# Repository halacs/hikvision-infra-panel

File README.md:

# Infra panel designs Hikvision IP cameras

After a few months/years infra LEDs are gone and need to be replaced. Since there are no cheap replacement boards on the internet I made my own based on the original factory infra panel.

I used KiCad 8.0 and Ubuntu 22.04 LTS. I add the final gerber finels and some pictures as well to the repository.

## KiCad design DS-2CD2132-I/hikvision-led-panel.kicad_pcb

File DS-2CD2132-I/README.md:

# Infra panel for Hikvision DS-2CD2132-I

However, I designed this infra panel for my Hikvision DS-2CD2132-I cameras, it might fit for other Hikvision models too. I have no experience with other models yet. If you have please let me know, either via a pull request or in any other way. Thanks!

I noticed that I drawn my PCB maybe with too thin wirings so be careful with the lines near to the edges of the PCB. I cut one line off while I was placing the parts...

# Parts

- 1 pc socket: JOINT TECH A1250WV-4P
- 30 pcs 3mm 850 nm infrared LEDs
- 1 pcs BPV10NF 5mm 950nm photodiode (or L-93DP3BT 3mm phototransistor)

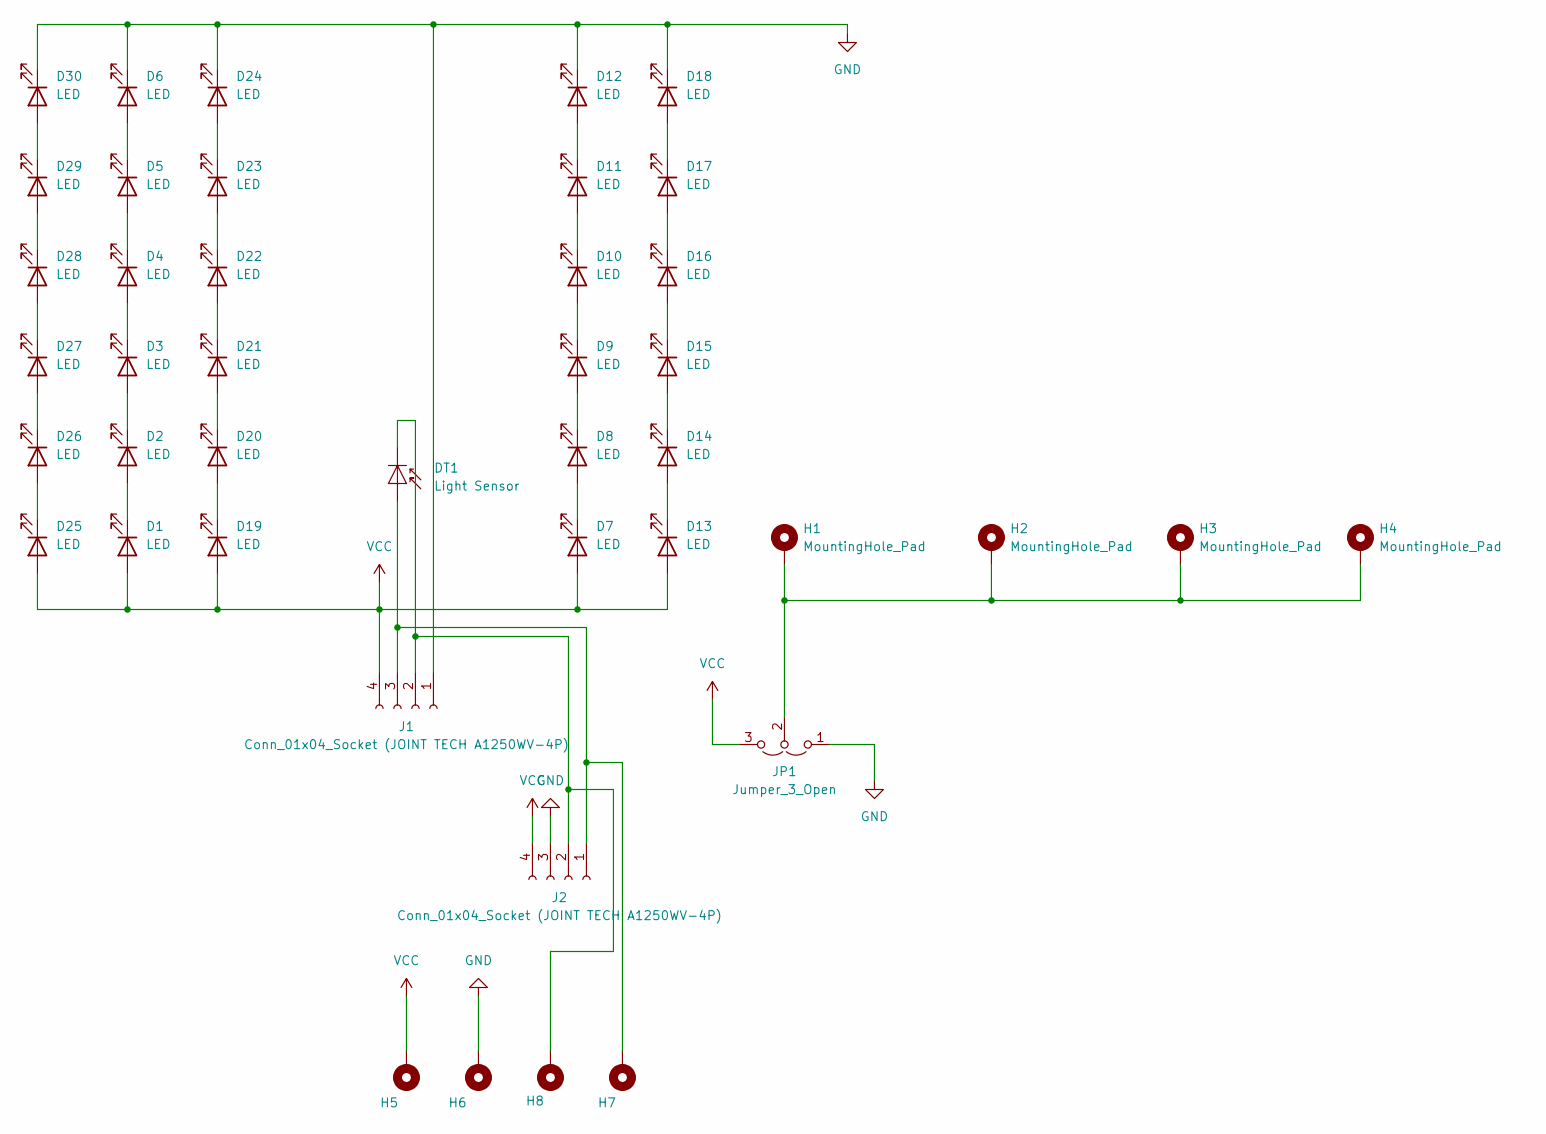
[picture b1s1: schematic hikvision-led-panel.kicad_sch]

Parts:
D1, D2, D3, D4, D5, D6, D7, D8, D9, D10, D11, D12, D13, D14, D15, D16, D17, D18, D19, D20, D21, D22, D23, D24, D25, D26, D27, D28, D29, D30: LED; LED_D3.0mm
DT1: Light Sensor; LED_D5.0mm
H1, H2, H3, H4: MountingHole_Pad; MountingHole_2.2mm_M2_DIN965_Pad
H5, H6, H7, H8: PinHeader_1x01_P2.54mm_Vertical
J1, J2: Conn_01x04_Socket (JOINT TECH A1250WV-4P); PinHeader_1x04_P1.27mm_Vertical
JP1: Jumper_3_Open; PinHeader_1x03_P2.54mm_Vertical

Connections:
GND: D6.1 (K), D12.1 (K), D18.1 (K), D24.1 (K), D30.1 (K), H6.1, J1.1, J2.3, JP1.1 (A)
unnamed: D1.1 (K), D2.2 (A)
unnamed: D2.1 (K), D3.2 (A)
unnamed: D3.1 (K), D4.2 (A)
unnamed: D4.1 (K), D5.2 (A)
unnamed: D5.1 (K), D6.2 (A)
unnamed: D7.1 (K), D8.2 (A)
unnamed: D8.1 (K), D9.2 (A)
unnamed: D9.1 (K), D10.2 (A)
unnamed: D10.1 (K), D11.2 (A)
unnamed: D11.1 (K), D12.2 (A)
unnamed: D13.1 (K), D14.2 (A)
unnamed: D14.1 (K), D15.2 (A)
unnamed: D15.1 (K), D16.2 (A)
unnamed: D16.1 (K), D17.2 (A)
unnamed: D17.1 (K), D18.2 (A)
unnamed: D19.1 (K), D20.2 (A)
unnamed: D20.1 (K), D21.2 (A)
unnamed: D21.1 (K), D22.2 (A)
unnamed: D22.1 (K), D23.2 (A)
unnamed: D23.1 (K), D24.2 (A)
unnamed: D25.1 (K), D26.2 (A)
unnamed: D26.1 (K), D27.2 (A)
unnamed: D27.1 (K), D28.2 (A)
unnamed: D28.1 (K), D29.2 (A)
unnamed: D29.1 (K), D30.2 (A)
unnamed: DT1.2 (A), H7.1, J1.3, J2.1
unnamed: DT1.1 (K), H8.1, J1.2, J2.2
unnamed: H1.1, H2.1, H3.1, H4.1, JP1.2 (C)
VCC: D1.2 (A), D7.2 (A), D13.2 (A), D19.2 (A), D25.2 (A), H5.1, J1.4, J2.4, JP1.3 (B)

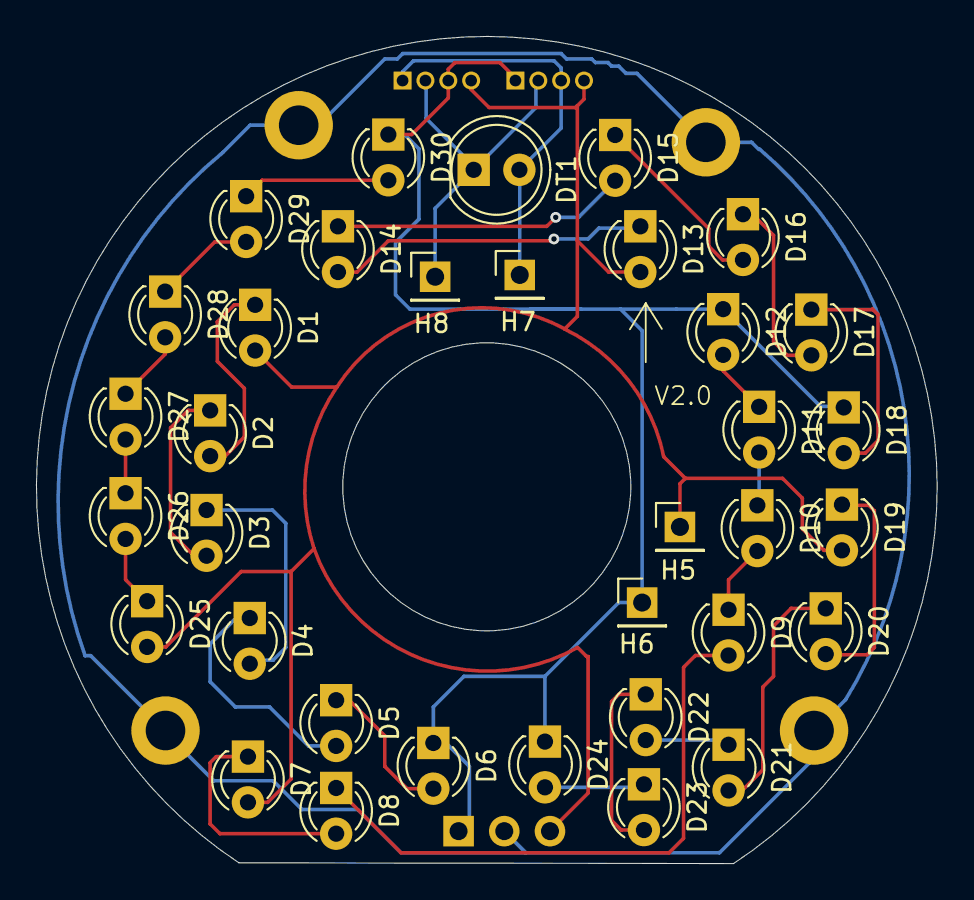
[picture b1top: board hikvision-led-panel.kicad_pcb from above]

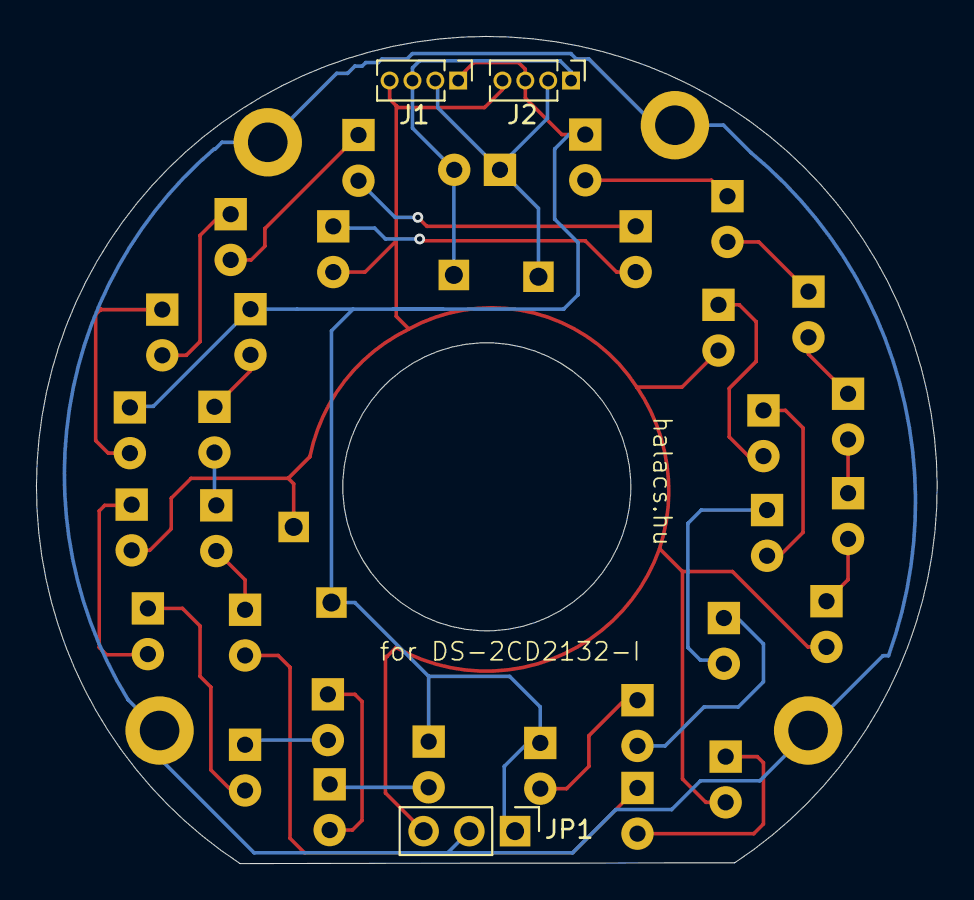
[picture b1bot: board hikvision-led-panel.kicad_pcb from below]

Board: 2 copper layers, 50.0 x 46.0 mm, 42 parts (3 on the bottom side), 30 nets.

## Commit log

2024-10-12 README.md
